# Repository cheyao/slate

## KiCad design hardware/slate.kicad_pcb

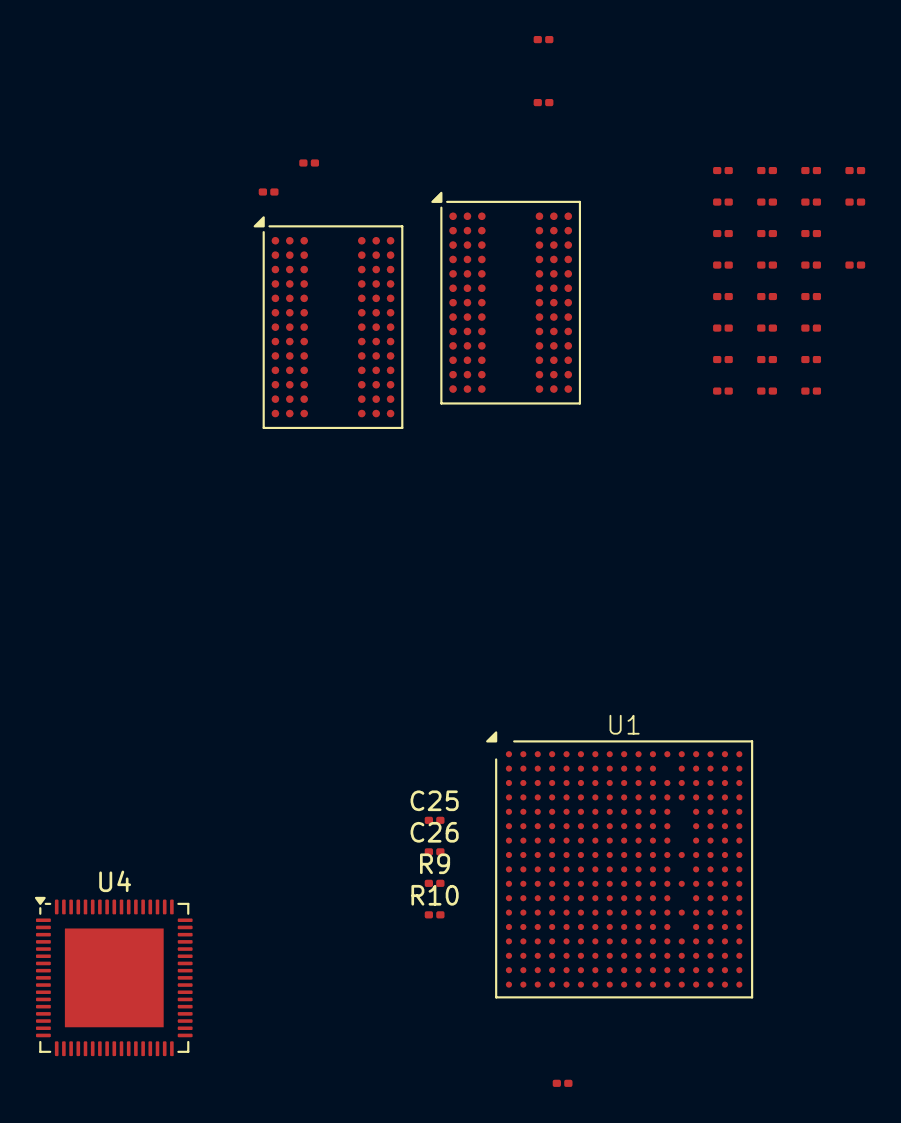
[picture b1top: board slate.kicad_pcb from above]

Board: 4 copper layers, 40 parts (0 on the bottom side), 55 nets, no tracks yet.

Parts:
C1, C2, C3, C4, C5, C6, C7, C8, C9, C10, C11, C12, C13, C14, C15, C16, C17, C18, C19, C20, C21, C22, C23, C24, C25, C26: 100n; C_0201_0603Metric
R1, R4, R6, R7, R8: 240; R_0201_0603Metric
R2, R3, R9, R10: 1k; R_0201_0603Metric
R5: 2k; R_0201_0603Metric
U1: A33; TFBGA-282_14x14mm_Layout17x17_P0.8mm
U2, U3: H5TQ4G83EFR; FBGA-78_7.5x11mm_Layout2x3x13_P0.8mm
U4: AXP223; QFN-68-1EP_8x8mm_P0.4mm_EP5.49x5.49mm

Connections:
+1V5: C2.1, C5.1, C6.1, C7.1, C8.1, C9.1, C10.1, C11.1, C12.1, C13.1, C14.1, C15.1, C16.1, C17.1, C18.1, C19.1, C20.1, C21.1, C22.1, C23.1, C24.1, C25.1, R2.1, R5.1, R9.1, U1.H5 (VCC-DRAM), U1.H6 (VCC-DRAM), U1.J5 (VCC-DRAM), U1.J6 (VCC-DRAM), U1.K5 (VCC-DRAM), U1.L5 (VCC-DRAM), U2.A2 (VDD), U2.A9 (VDD), U2.B9 (VDDQ), U2.C1 (VDDQ), U2.D7 (VDD), U2.E2 (VDDQ), U2.E9 (VDDQ), U2.G2 (VDD), U2.G8 (VDD), U2.K1 (VDD), U2.K9 (VDD), U2.M1 (VDD), U2.M9 (VDD), U3.A2 (VDD), U3.A9 (VDD), U3.B9 (VDDQ), U3.C1 (VDDQ), U3.D7 (VDD), U3.E2 (VDDQ), U3.E9 (VDDQ), U3.G2 (VDD), U3.G8 (VDD), U3.K1 (VDD), U3.K9 (VDD), U3.M1 (VDD), U3.M9 (VDD)
/A33/A0: U1.E4 (DA0), U2.K3 (A0), U3.K3 (A0)
/A33/A1: U1.D1 (DA1), U2.L7 (A1), U3.L7 (A1)
/A33/A2: U1.F2 (DA2), U2.L3 (A2), U3.L3 (A2)
/A33/A3: U1.H3 (DA3), U2.K2 (A3), U3.K2 (A3)
/A33/A4: U1.D2 (DA4), U2.L8 (A4), U3.L8 (A4)
/A33/A5: U1.F1 (DA5), U2.L2 (A5), U3.L2 (A5)
/A33/A6: U1.A1 (DA6), U2.M8 (A6), U3.M8 (A6)
/A33/A7: U1.G4 (DA7), U2.M2 (A7), U3.M2 (A7)
/A33/A8: U1.B1 (DA8), U2.N8 (A8), U3.N8 (A8)
/A33/A9: U1.F4 (DA9), U2.M3 (A9), U3.M3 (A9)
/A33/A10: U1.E2 (DA10), U2.H7 (A10/AP), U3.H7 (A10/AP)
/A33/A11: U1.C2 (DA11), U2.M7 (A11), U3.M7 (A11)
/A33/A12: U1.E1 (DA12), U2.K7 (A12/~BC), U3.K7 (A12/~BC)
/A33/A13: U1.F3 (DA13), U2.N3 (A13), U3.N3 (A13)
/A33/A14: U1.C1 (DA14), U2.N7 (A14), U3.N7 (A14)
/A33/A15: U1.E3 (DA15), U2.J7 (A15), U3.J7 (A15)
/A33/BA0: U1.J3 (DBA0), U2.J2 (BA0), U3.J2 (BA0)
/A33/BA1: U1.K4 (DBA1), U2.K8 (BA1), U3.K8 (BA1)
/A33/BA2: U1.H4 (DBA2), U2.J3 (BA2), U3.J3 (BA2)
/A33/CKE0: U1.J4 (DCKE), U2.G9 (CKE0), U3.G9 (CKE0)
/A33/CKE1: U1.N7 (DCKE1), U2.F9 (CKE1/NC), U3.F9 (CKE1/NC)
/A33/CLK+: U1.G1 (DCK), U2.F7 (CK), U3.F7 (CK)
/A33/CLK-: U1.G2 (DCKB), U2.G7 (~CK), U3.G7 (~CK)
/A33/DQM0: U1.N2 (DQM0), U2.B7 (DM/TDQS)
/A33/DQM1: U1.T3 (DQM1), U3.B7 (DM/TDQS)
/A33/DQS0+: U1.K2 (DQS0), U2.C3 (DQS)
/A33/DQS0-: U1.K1 (DQS0B), U2.D3 (~DQS)
/A33/DQS1+: U1.R1 (DQS1), U3.C3 (DQS)
/A33/DQS1-: U1.T1 (DQS1B), U3.D3 (~DQS)
/A33/ODT0: U1.L3 (DODT), U2.G1 (ODT0), U3.G1 (ODT0)
/A33/ODT1: U1.L7 (DODT1), U2.F1 (ODT1/NC), U3.F1 (ODT1/NC)
/A33/~CAS: U1.M3 (DCAS), U2.G3 (~CAS), U3.G3 (~CAS)
/A33/~CS0: U1.N3 (DCS), U2.H2 (~CS0), U3.H2 (~CS0)
/A33/~CS1: U1.N5 (DCS1), U2.H1 (~CS1/NC), U3.H1 (~CS1/NC)
/A33/~RAS: U1.L4 (DRAS), U2.F3 (~RAS), U3.F3 (~RAS)
/A33/~RESET: R5.2, U1.G3 (DRST), U2.N2 (~RESET), U3.N2 (~RESET)
/A33/~WE: U1.K3 (DWE), U2.H3 (~WE), U3.H3 (~WE)
/Power/IPSOUT: U4.1 (ELDOIN), U4.9 (VIN5), U4.13 (VIN1), U4.18 (DLDOIN), U4.23 (VIN2), U4.40 (LX3), U4.41 (LX3), U4.53 (IPSOUT), U4.54 (IPSOUT), U4.62 (VIN_CHG), U4.63 (VIN_CHG), U4.65 (LX4)
ACIN: U4.55 (ACIN), U4.56 (ACIN)
GND: C1.2, C3.2, C4.2, C5.2, C6.2, C7.2, C8.2, C9.2, C10.2, C11.2, C12.2, C13.2, C14.2, C15.2, C16.2, C17.2, C18.2, C19.2, C20.2, C21.2, C22.2, C23.2, C24.2, C26.2, R1.2, R3.2, R4.2, R6.2, R7.2, R8.2, R10.2, U1.F8 (GND), U1.F9 (GND), U1.F10 (GND), U1.G7 (GND), U1.G8 (GND), U1.G9 (GND), U1.G10 (GND), U1.G11 (GND), U1.H7 (GND), U1.H8 (GND), U1.H9 (GND), U1.H10 (GND), U1.H11 (GND), U1.H12 (GND), U1.H13 (AGND), U1.J7 (GND), U1.J8 (GND), U1.J9 (GND), U1.J10 (GND), U1.J11 (GND), U1.J12 (GND), U1.K7 (GND), U1.K8 (GND), U1.K9 (GND), U1.K10 (GND), U1.K11 (GND), U1.K12 (GND), U1.L8 (GND), U1.L9 (GND), U1.L10 (GND), U1.L11 (GND), U1.M9 (GND), U1.M10 (GND), U1.N4 (GND), U2.A1 (VSS), U2.A8 (VSS), U2.B1 (VSS), U2.B2 (VSSQ), U2.B8 (VSSQ), U2.C9 (VSSQ), U2.D1 (VSSQ), U2.D8 (VSS), U2.D9 (VSSQ), U2.F2 (VSS), U2.F8 (VSS), U2.J1 (VSS), U2.J9 (VSS), U2.L1 (VSS), U2.L9 (VSS), U2.N1 (VSS), U2.N9 (VSS), U3.A1 (VSS), U3.A8 (VSS), U3.B1 (VSS), U3.B2 (VSSQ), U3.B8 (VSSQ), U3.C9 (VSSQ), U3.D1 (VSSQ), U3.D8 (VSS), U3.D9 (VSSQ), U3.F2 (VSS), U3.F8 (VSS), U3.J1 (VSS), U3.J9 (VSS), U3.L1 (VSS), U3.L9 (VSS), U3.N1 (VSS), U3.N9 (VSS), U4.6 (PGND5), U4.15 (PGND1), U4.26 (PGND2), U4.27 (PGND2), U4.42 (PGND3), U4.59 (PGND_CHG), U4.66 (PGND4), U4.69 (GND)
unnamed: C25.2, C26.1, R9.2, R10.1, U1.M4 (DVREF)
unnamed: R6.1, U1.R3 (DZQ)
unnamed: C1.1, C2.2, C3.1, C4.1, R2.2, R3.1, U2.E1 (VREFDQ), U2.J8 (VREFCA), U3.E1 (VREFDQ), U3.J8 (VREFCA)
unnamed: R1.1, U2.H8 (ZQ0)
unnamed: R7.1, U2.H9 (ZQ1/NC)
unnamed: R4.1, U3.H8 (ZQ0)
unnamed: R8.1, U3.H9 (ZQ1/NC)
unnamed: U4.24 (LX2), U4.25 (LX2)
unnamed: U4.7 (LX5), U4.8 (LX5)
unnamed: U4.60 (LX_CHG), U4.61 (LX_CHG)
VCC-IO: U1.E11 (VCC-IO), U1.E12 (VCC-IO), U1.F11 (VCC-IO), U1.F12 (VCC-IO), U1.G12 (VCC-IO)
VCC-PD: U1.M11 (VCC-PD), U1.N11 (VCC-PD)
VDD-CPU: U1.E5 (VDD-CPU), U1.E6 (VDD-CPU), U1.E7 (VDD-CPU), U1.F5 (VDD-CPU), U1.F6 (VDD-CPU), U1.F7 (VDD-CPU), U1.G5 (VDD-CPU), U1.G6 (VDD-CPU)
VDD-SYS: U1.E8 (VDD-SYS), U1.E9 (VDD-SYS), U1.E10 (VDD-SYS), U1.K6 (VDD-SYS), U1.L6 (VDD-SYS), U1.M6 (VDD-SYS), U1.M7 (VDD-SYS), U1.N8 (VDD-SYS), U1.N9 (VDD-SYS), U1.N10 (VDD-SYS)

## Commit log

2025-05-30 Init
2025-05-30 TFBGA282 P0.8mm footprint
2025-06-07 DDR3 RAM symbol
2025-06-07 DDR3 schematic made
2025-06-15 Start of psu
2025-06-15 PMU 90% done
